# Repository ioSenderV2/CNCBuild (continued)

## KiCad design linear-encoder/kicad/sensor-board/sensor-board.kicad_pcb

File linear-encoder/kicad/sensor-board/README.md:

# Sensor board - KiCad

Schematic for the board described in [`../../sensor-board.md`](../../sensor-board.md).

| File | |
|---|---|
| `sensor-board.kicad_sch` | The schematic. Symbols are **embedded** (`lib_symbols`), so it needs no external libraries. |
| `sensor-board.kicad_pro` | Project wrapper. |
| `netlist.txt` | The connection list, generated from the same source as the schematic. |
| `generate.py` | The seed that produced the first version. See the warning below. |

> FLAG: **`generate.py` is already a SEED, not the source of truth - as of 2026-08-29.**
> It took one `kicad-cli sch erc` run: the tool **re-saves the schematic**, upgrading it from the
> `version 20231120` header the script writes to KiCad 10's own format (and to CRLF, which
> `.gitattributes` normalises back to LF on commit). Nobody opened Eeschema; running the checks was
> enough. **Re-running `generate.py` now overwrites whatever KiCad wrote, including any layout or
> hand edits.** Treat the `.kicad_sch` as the live document, keep the script as the record of how the
> netlist was derived, and if the design changes, edit in Eeschema and update `netlist.txt` to match.
>
> Connectivity was re-checked **after** the upgrade: all 12 nets and every node still identical, and
> all 9 `no_connect` markers intact. The format change carried the design across without loss.

## Status: verified against KiCad 10.0.5

Checked with `kicad-cli`, not just written and hoped for:

| Check | Result |
|---|---|
| Parses / loads | **Yes** - `sch erc` and `sch export netlist` both succeed |
| Netlist matches `netlist.txt` | **Exactly.** All 12 connected nets, every node identical, nothing extra or missing |
| `no_connect` coverage | **9 pins - 1, 6, 7, 10, 11, 15, 16, 17, 20** - exactly the datasheet's NC list plus Index and PWM |
| ERC violations | **12**, all one warning type - see below |

Reproduce with:

```
kicad-cli sch erc --severity-all --output erc-report.txt sensor-board.kicad_sch
kicad-cli sch export netlist --format kicadsexpr --output kicad-export.net sensor-board.kicad_sch
```

### The 12 violations are all expected

Every one is `lib_symbol_issues`: *"The current configuration does not include the symbol library
'cnc'"*. The symbols are embedded in the file rather than coming from a configured library, so KiCad
notes it. Nothing is broken - and as on the controller board the warning is arguably useful, because
those symbols **are** placeholders.

## Symbols are placeholders - swap before layout

`cnc:AS5311`, `cnc:RJ45_8_UNSHLD`, `cnc:TVS_4`, `cnc:R`, `cnc:C`, `cnc:TP` are minimal rectangles with
correct pin numbering and, on the AS5311, correct pin names from datasheet Table 1. Enough to carry
the netlist; not real parts. Before layout:

- **The RJ45 footprint is the open question, not a detail.** Unshielded, vertical, no magnetics - and
  whether it can be through-hole at all is unresolved. `../../sensor-board.md` has the height budget
  and the options. **Do not lay this board out until that is settled**, because it decides the part.
- **The AS5311 footprint is the one dimension that matters.** The datasheet's recommended land
  pattern is A 7.00, B 5.00, C 0.38, D 0.65, E 6.23 mm (rev 1.12 §9.1, Fig 18). What actually decides
  accuracy is the **Hall array position relative to the package's reference edges**, from Figure 14 -
  and that figure was read off a rendered page, so confirm those edges first.
- Expect a "no power source" ERC complaint once real power symbols are used: `+3V3` arrives through
  a passive connector pin, which is honest for a board at the end of a cable. A `PWR_FLAG` settles it.

## How it is drawn

**Connections are by net label on a short stub at each pin**, not point-to-point wires - the same
convention as the controller board, for the same reason. It reads as a fan-out list, which is what
the board is.

Net names ending `_SRC` are the chip side of a series resistor; the bare name is the cable side. So
`A_SRC` is `U1` pin 4, `A` is what reaches the jack.

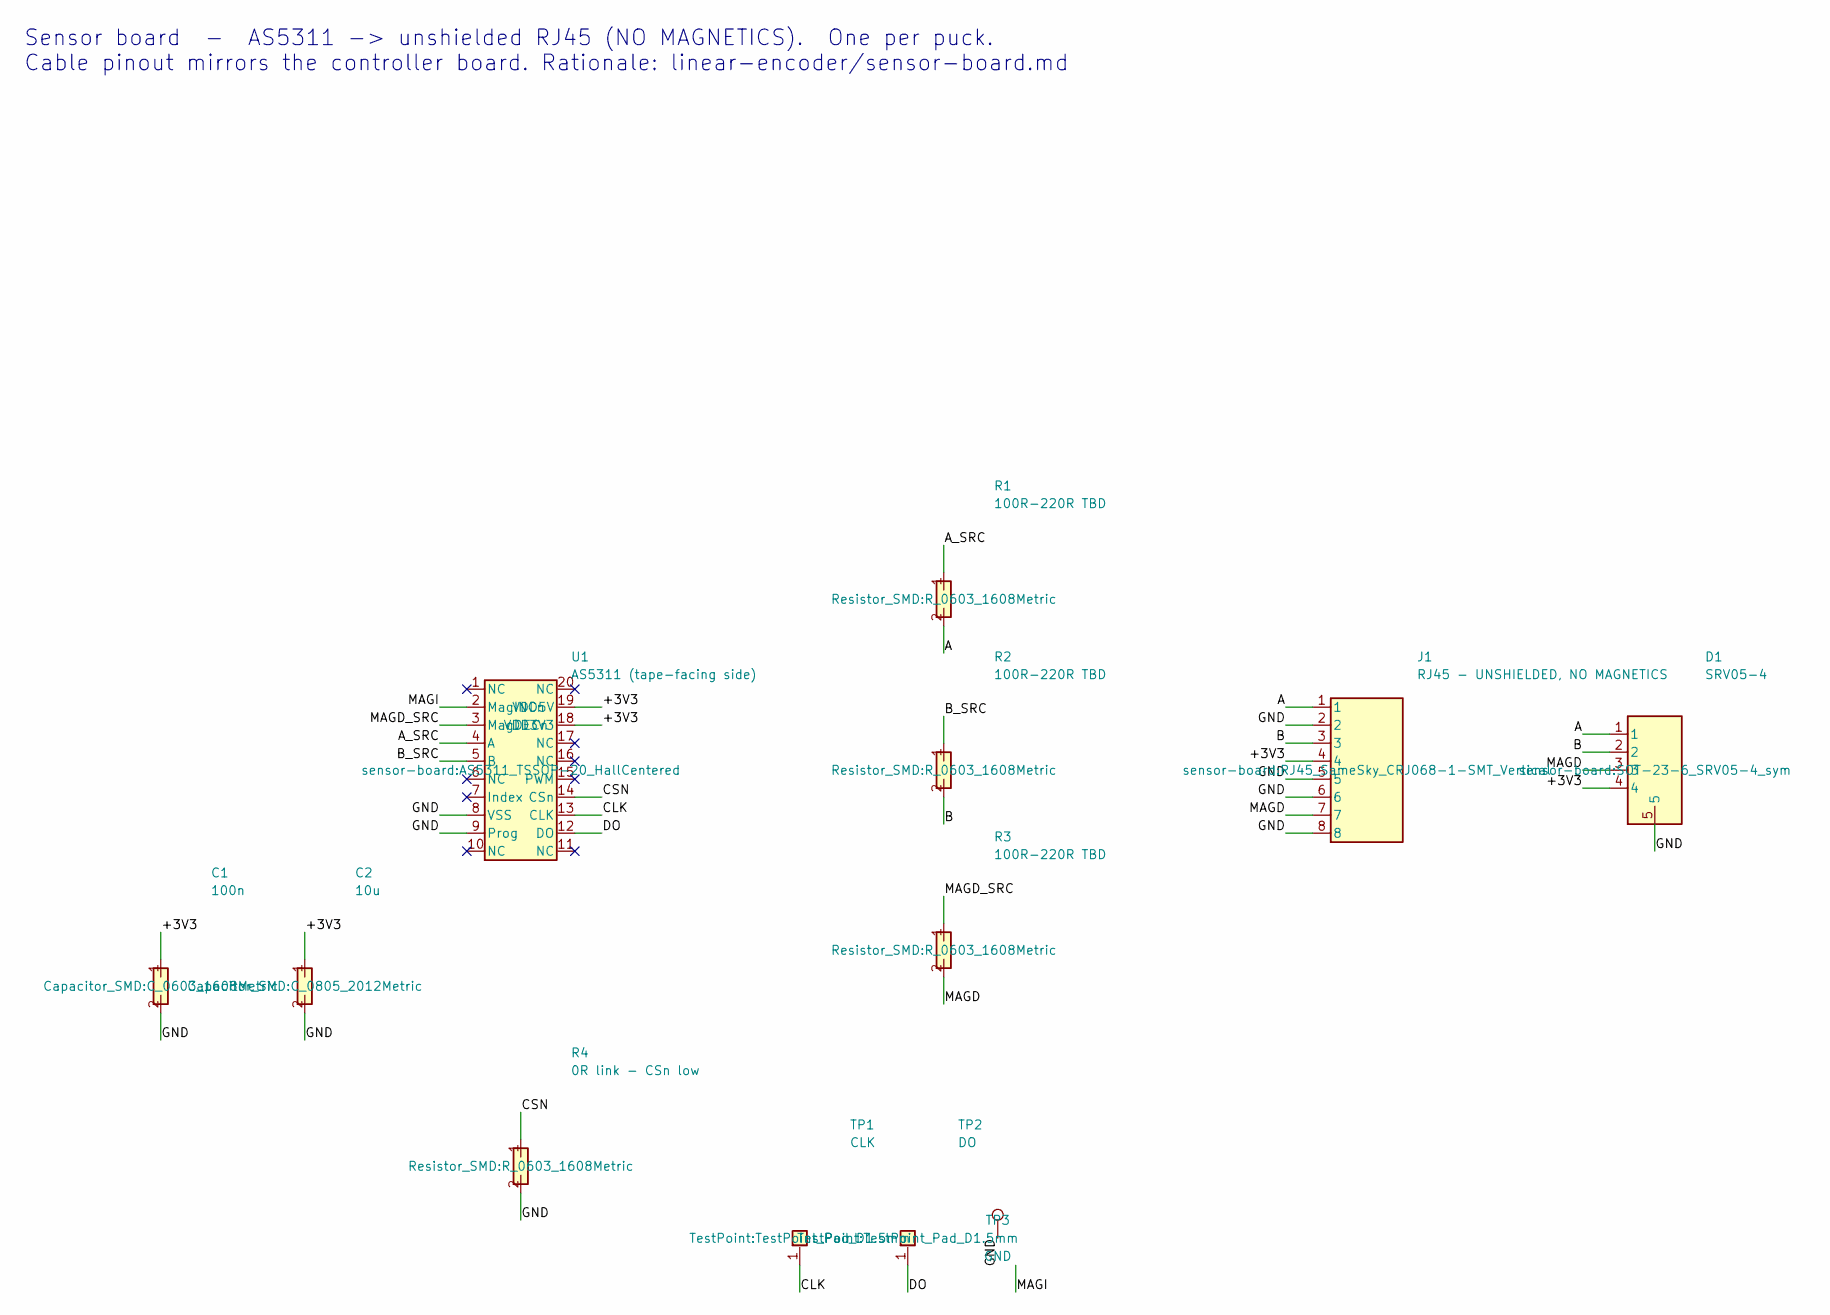
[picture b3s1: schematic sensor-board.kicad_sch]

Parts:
C1: 100n; C_0603_1608Metric
C2: 10u; C_0805_2012Metric
D1: SRV05-4; SOT-23-6_SRV05-4_sym
J1: RJ45 - UNSHIELDED, NO MAGNETICS; RJ45_SameSky_CRJ068-1-SMT_Vertical
R1, R2, R3: 100R-220R TBD; R_0603_1608Metric
R4: 0R link - CSn low; R_0603_1608Metric
TP1: CLK; TestPoint_Pad_D1.5mm
TP2: DO; TestPoint_Pad_D1.5mm
TP3: GND; TestPoint_Pad_D1.5mm
U1: AS5311 (tape-facing side); AS5311_TSSOP-20_HallCentered

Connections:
+3V3: C1.1, C2.1, D1.4, J1.4, U1.18 (VDD3V3), U1.19 (VDD5V)
A: D1.1, J1.1, R1.2
A_SRC: R1.1, U1.4 (A)
B: D1.2, J1.3, R2.2
B_SRC: R2.1, U1.5 (B)
CLK: TP1.1, U1.13 (CLK)
CSN: R4.1, U1.14 (CSn)
DO: TP2.1, U1.12 (DO)
GND: C1.2, C2.2, D1.5, J1.2, J1.5, J1.6, J1.8, R4.2, TP3.1, U1.8 (VSS), U1.9 (Prog)
MAGD: D1.3, J1.7, R3.2
MAGD_SRC: R3.1, U1.3 (MagDECn)
MAGI: U1.2 (MagINCn)

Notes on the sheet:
Sensor board - AS5311 -> unshielded RJ45 (NO MAGNETICS). One per puck. Cable pinout mirrors the controller board. Rationale: linear-encoder/sensor-board.md

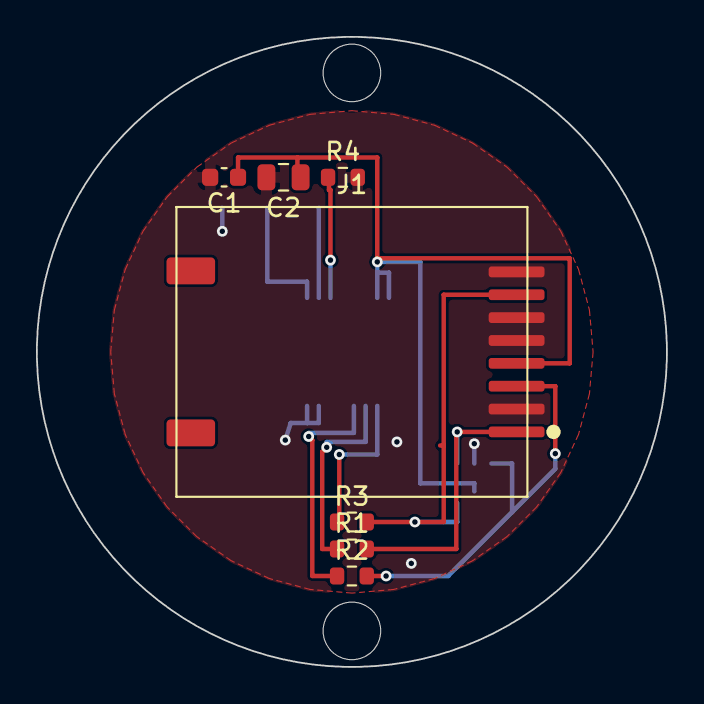
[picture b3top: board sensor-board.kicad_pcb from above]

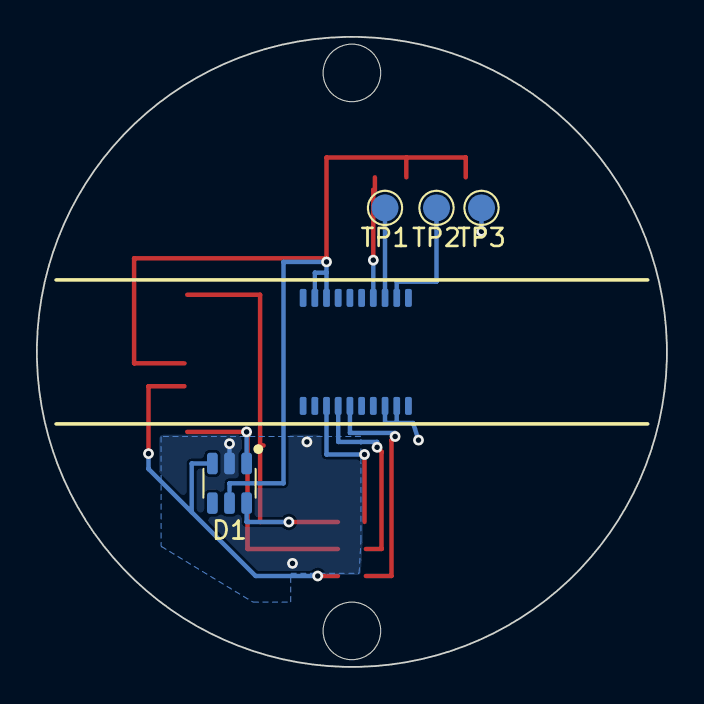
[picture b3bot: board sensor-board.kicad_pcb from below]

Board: 2 copper layers, 35.0 x 35.0 mm, 14 parts (5 on the bottom side), 11 nets.

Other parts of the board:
MH1, MH2: MountingHole_3.2mm

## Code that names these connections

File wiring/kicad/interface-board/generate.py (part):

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  2x10 IDC  - ribbon to RP23 J20, mirrored pin-for-pin
  2x3  IDC  - ribbon to RP23 J24 servo alarm header, per-axis parallel
  screw terminal blocks: 12V in (from the 36V->12V buck), 12V out (to the RP23's
  power inputs), 5P limits, 4P spindle, 2P probe+door

Axis mapping: the Y1 jack drives the controller's Y, the Y2 jack drives A.

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    place("cnc:CONN_1x03", "J%d" % (i + 6), "Mini-Fit 3P - %s prox" % lab,
          125, y, rec("J%d" % (i + 6), px))

# Probe family and spindle, bottom row.
place("cnc:CONN_1x03", "J11", "Mini-Fit 3P - 3D probe",
      60, 272, rec("J11", {1: "+12V", 2: "PROBE", 3: "GND"}))
place("cnc:CONN_1x03", "J12", "Mini-Fit 3P - toolsetter",
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place("cnc:CONN_1x02", "J14", "Mini-Fit 2P - touch probe 2",
      240, 272, rec("J14", {1: "PROBE", 2: "GND"}))
place("cnc:CONN_1x04", "J15", "Mini-Fit 4P - spindle",
      300, 272, rec("J15", {1: "SPIN_EN", 2: "GND", 3: "GND", 4: "SPIN_PWM"}))

# Controller side. J16 mirrors RP23 J20 pin-for-pin (1:1 ribbon, pin 1 to pin 1).
J20_MAP = {}
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      240, 120, rec("J21", {1: "LIM_X", 2: "LIM_Y", 3: "LIM_A",
                            4: "LIM_Z", 5: "LIM_B"}))
place("cnc:TB_1x04", "J22", "TB 4P - spindle to RP23",
      240, 165, rec("J22", {1: "SPIN_EN", 2: "GND", 3: "GND", 4: "SPIN_PWM"}))
place("cnc:TB_1x02", "J23", "TB 2P - probe + door to RP23",
      240, 205, rec("J23", {1: "PROBE", 2: "DOOR"}))

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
